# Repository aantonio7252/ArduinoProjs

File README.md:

Various Arduino Projects by Antonio Chang

Currently only includes minithing - An Arduino Nano sensor hub with lithium-ion battery charging. Connects sensors using I2C communication, with an AHT20 temperature and humidity sensor, DS3231 real-time clock, MCP23008 expander for buttons, and a 128x64 OLED display.

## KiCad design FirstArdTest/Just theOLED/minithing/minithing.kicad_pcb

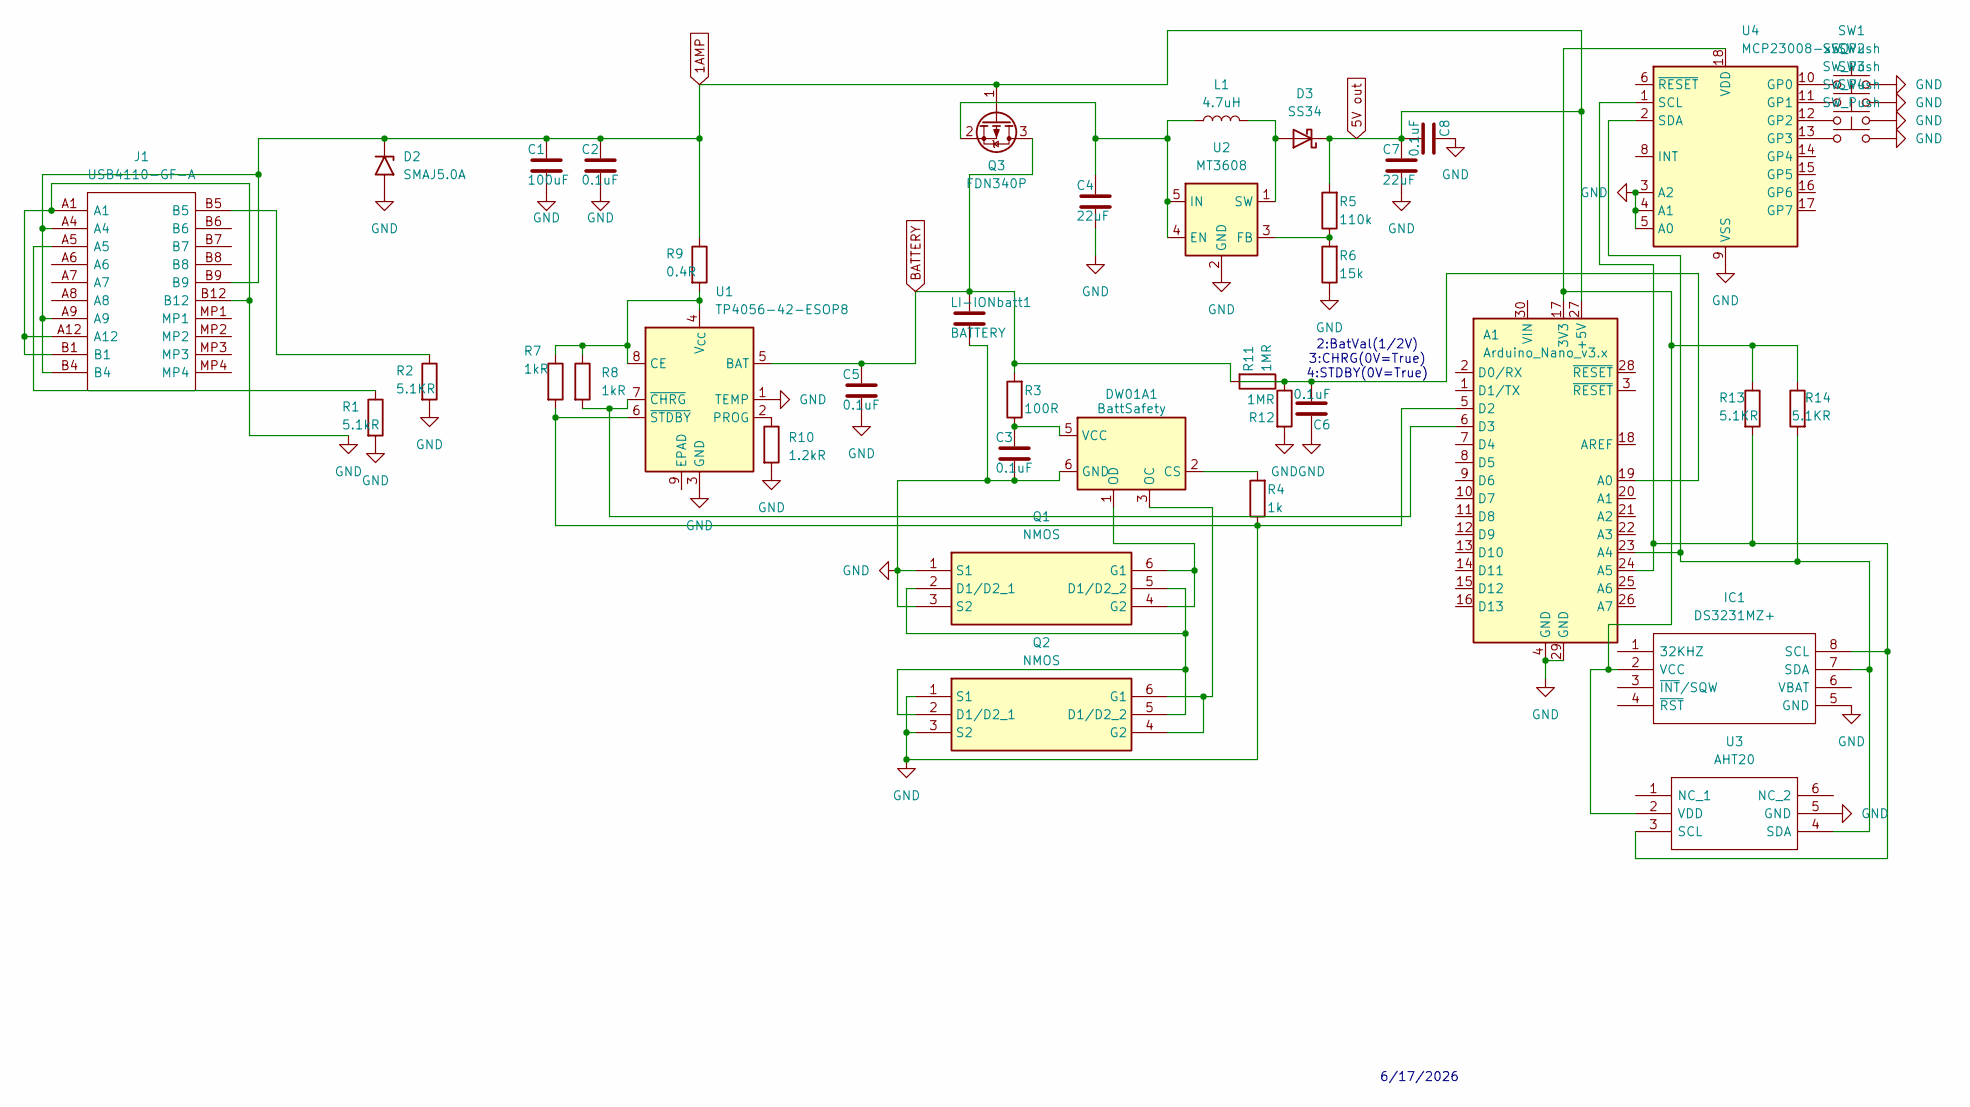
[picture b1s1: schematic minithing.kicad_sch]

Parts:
A1: Arduino_Nano_v3.x; Arduino_Nano
C1: 100uF; C_1206_3216Metric_Pad1.33x1.80mm_HandSolder
C2, C3, C5, C6, C8: 0.1uF; C_0805_2012Metric_Pad1.18x1.45mm_HandSolder
C4, C7: 22uF; C_1206_3216Metric_Pad1.33x1.80mm_HandSolder
D2: SMAJ5.0A; D_SMA
D3: SS34; D_SMC_Handsoldering
DW01A1: BattSafety; SOT-23-6
IC1: DS3231MZ+; SOIC127P600X175-8N; Manufacturer_Part_Number DS3231MZ+; Mouser Part Number 700-DS3231MZ+
J1: USB4110-GF-A; USB4110GFA; Manufacturer_Part_Number USB4110-GF-A; Mouser Part Number 640-USB4110-GF-A
L1: 4.7uH; L_0805_2012Metric_Pad1.15x1.40mm_HandSolder
LI-IONbatt1: BATTERY; BatteryHolder_Keystone_1042_1x18650
Q1, Q2: NMOS; SOT95P280X125-6N; Manufacturer_Part_Number FS8205A
Q3: FDN340P; SOT-23
R1: 5.1kR; R_0805_2012Metric_Pad1.20x1.40mm_HandSolder
R2, R13, R14: 5.1KR; R_0805_2012Metric_Pad1.20x1.40mm_HandSolder
R3: 100R; R_0805_2012Metric_Pad1.20x1.40mm_HandSolder
R4: 1k; R_0805_2012Metric_Pad1.20x1.40mm_HandSolder
R5: 110k; R_0805_2012Metric_Pad1.20x1.40mm_HandSolder
R6: 15k; R_0805_2012Metric_Pad1.20x1.40mm_HandSolder
R7, R8: 1kR; R_0805_2012Metric_Pad1.20x1.40mm_HandSolder
R9: 0.4R; R_1206_3216Metric_Pad1.30x1.75mm_HandSolder
R10: 1.2kR; R_0805_2012Metric_Pad1.20x1.40mm_HandSolder
R11, R12: 1MR; R_0805_2012Metric_Pad1.20x1.40mm_HandSolder
SW1, SW2, SW3, SW4: SW_Push; SW_PUSH_6mm
U1: TP4056-42-ESOP8; SOIC-8-1EP_3.9x4.9mm_P1.27mm_EP2.41x3.3mm_ThermalVias
U2: MT3608; SOT-23-6
U3: AHT20; Manufacturer_Part_Number AHT20
U4: MCP23008-xSO; SOIC-18W_7.5x11.6mm_P1.27mm

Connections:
1AMP: A1.27 (+5V), C1.1, C2.1, C7.1, C8.2, D2.1 (A1), D3.1 (K), J1.A4, J1.A9, J1.B4, J1.B9, Q3.1 (G), R5.2, R9.1
BATTERY: C5.1, LI-IONbatt1.1, Q3.3 (D), R3.2, R11.2, U1.5 (BAT)
GND: A1.4 (GND), A1.5 (D2), A1.29 (GND), C1.2, C2.2, C3.2, C4.2, C5.2, C6.1, C7.2, C8.1, D2.2 (A2), DW01A1.6 (GND), IC1.5 (GND), J1.A1, J1.A12, J1.B1, J1.B12, LI-IONbatt1.2, Q1.1 (S1), Q1.3 (S2), Q2.1 (S1), Q2.3 (S2), R1.2, R2.2, R4.1, R6.1, R7.2, R10.2, R12.2, SW1.2, SW2.2, SW3.2, SW4.2, U1.1 (TEMP), U1.3 (GND), U1.6 (~STDBY), U2.2 (GND), U3.5 (GND), U4.3 (A2), U4.4 (A1), U4.5 (A0), U4.9 (VSS)
unnamed: A1.17 (3V3), IC1.2 (VCC), R13.1, R14.1, U3.2 (VDD), U4.18 (VDD)
unnamed: A1.19 (A0), C6.2, R11.1, R12.1
unnamed: A1.23 (A4), IC1.7 (SDA), R14.2, U3.4 (SDA), U4.2 (SDA)
unnamed: A1.24 (A5), IC1.8 (SCL), R13.2, U3.3 (SCL), U4.1 (SCL)
unnamed: A1.6 (D3), R8.2, U1.7 (~CHRG)
unnamed: D3.2 (A), L1.2, U2.1 (SW)
unnamed: DW01A1.2 (CS), R4.2
unnamed: DW01A1.3 (OC), Q2.4 (G2), Q2.6 (G1)
unnamed: DW01A1.1 (OD), Q1.4 (G2), Q1.6 (G1)
unnamed: C3.1, DW01A1.5 (VCC), R3.1
unnamed: J1.A5, R1.1
unnamed: J1.B5, R2.1
unnamed: Q1.2 (D1/D2_1), Q1.5 (D1/D2_2), Q2.2 (D1/D2_1), Q2.5 (D1/D2_2)
unnamed: C4.1, L1.1, Q3.2 (S), U2.4 (EN), U2.5 (IN)
unnamed: R7.1, R8.1, R9.2, U1.4 (V_{CC}), U1.8 (CE)
unnamed: R10.1, U1.2 (PROG)
unnamed: R5.1, R6.2, U2.3 (FB)
unnamed: SW1.1, U4.10 (GP0)
unnamed: SW2.1, U4.11 (GP1)
unnamed: SW3.1, U4.12 (GP2)
unnamed: SW4.1, U4.13 (GP3)

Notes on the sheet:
2:BatVal(1/2V) 3:CHRG(0V=True) 4:STDBY(0V=True)
6/17/2026

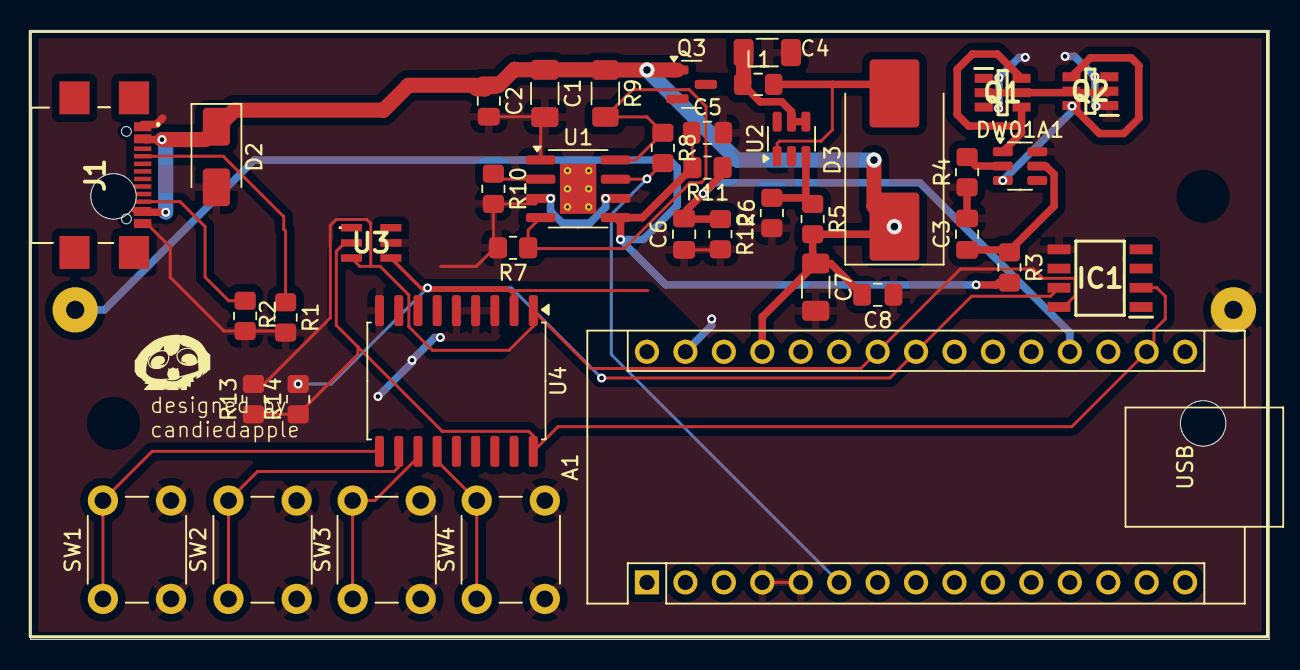
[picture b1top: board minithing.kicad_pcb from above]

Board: 2 copper layers, 81.8 x 40.2 mm, 41 parts (1 on the bottom side), 24 nets.

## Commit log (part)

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2026-04-11 Test
2026-05-06 Push for vibes
2026-05-22 Deleted
2026-05-22 Add project description to README
2026-05-31 Libraries and part 1 bpack complete
2026-06-06 PD realization commit
2026-06-17 Almost done schematic push
2026-06-18 Tahoe trip push
